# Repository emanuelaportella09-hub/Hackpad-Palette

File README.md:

# Hackpad-Palette
A Hackpad where you can switch colors on Paint for Windows 11.

I tried to make a keyboard for when I use Paint, to change colors like a real palette.

IT ONLY WORKS FOR PAINT ON WINDOWS 11.
IT WON'T WORK FOR OTHER SOFTWARE.

It was fun to make, and it taught me more about the production process of keyboards. It's really interesting, because out there is a whole community that loves this kind of hardware.

# FEATURES
- 128x32 OLED display
- 16 keys
- Can change colors on Paint on Windows 11

# PCB
I used EasyEDA for this project since I know how to use it a little, unlike KiCad.

# SCHEMATICS

# CAD
Plate only

Case and plate

Case, plate, and PCB all together. I couldn't put the 3D file of the PCB in Onshape because it was buggy for some reason, so I decided to put a rectangle inside with the same measurements as the board instead.

# BOM

16x MX Switches

1x XIAO RP2040

16x Differently Colored DSA Keycaps

4x M3x16 Bolt

4x M3 Heatset

1x 0.91" 128x32 OLED Display

16x Through-hole 1N4148 Diodes

1x Case.step in PRODUCTION FOLDER needs to be 3d printed

1x Plate.step in PRODUCTION FOLDER needs to be 3d printed

#**EXTRA NEDDED:**

Soldering Iron

My firmware

Arduino IDE installed on a computer

AutoHotKey installed on a computer

#**TESTING:**

Few Jump Wires

Breadboard

Usb-c to usb cable

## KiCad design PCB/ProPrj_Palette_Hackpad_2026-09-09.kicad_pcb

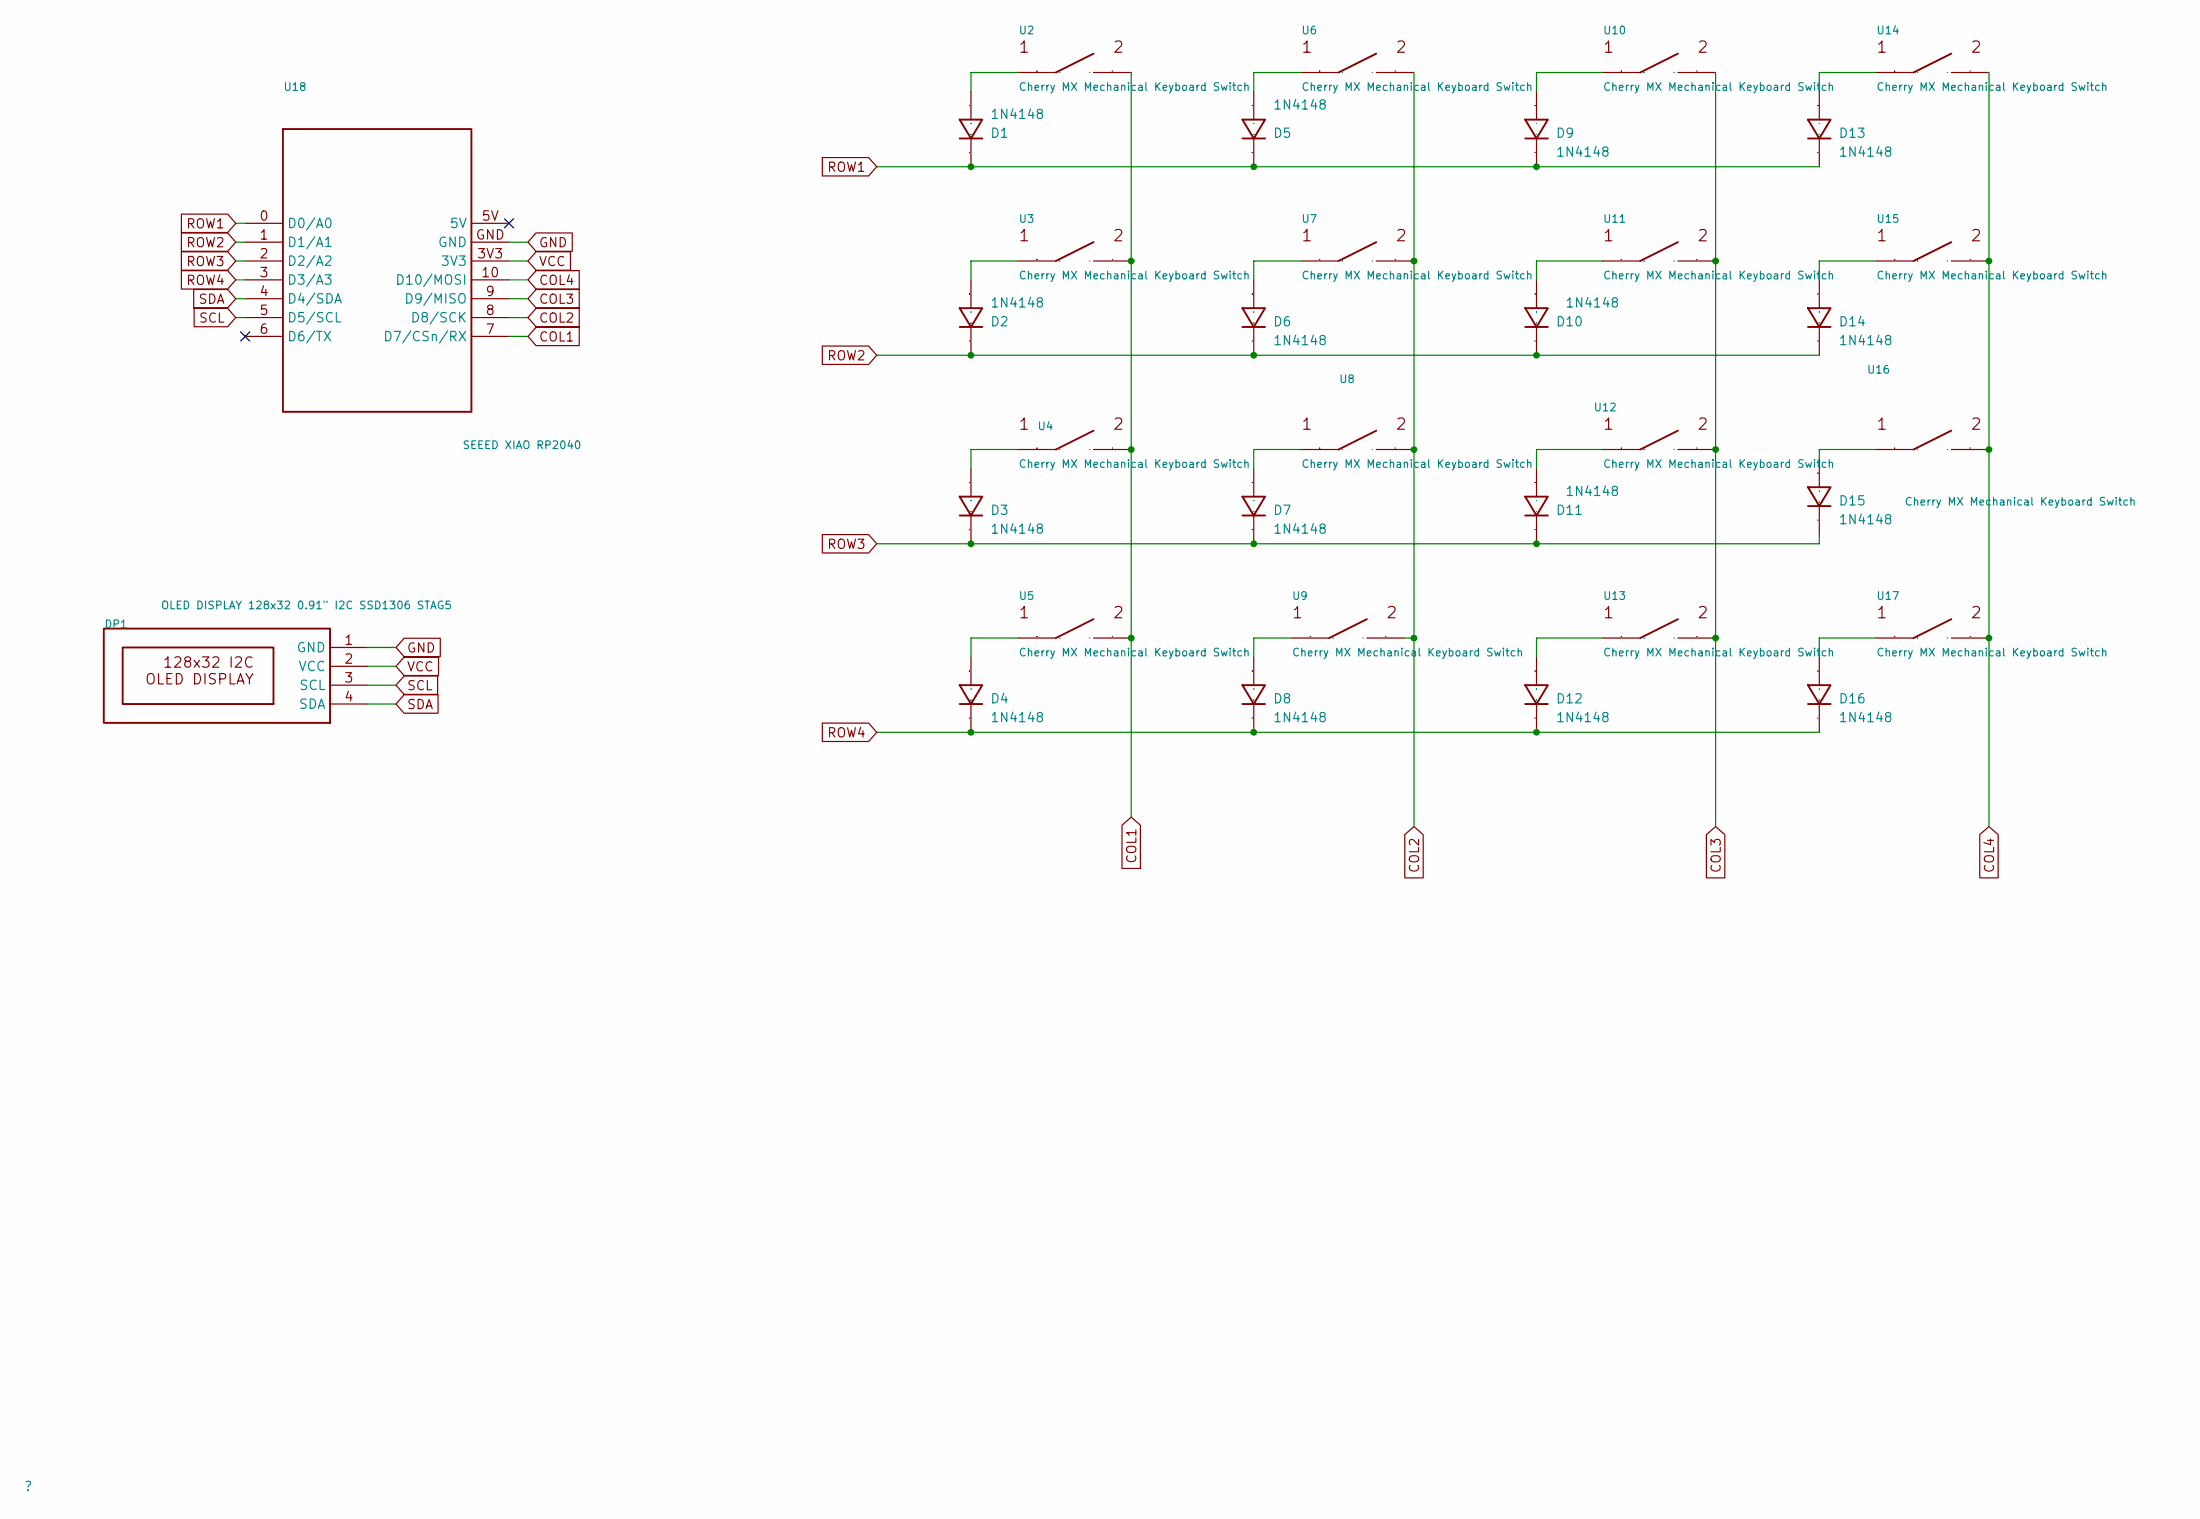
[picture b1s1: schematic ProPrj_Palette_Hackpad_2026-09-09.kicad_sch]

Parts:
D1, D2, D3, D4, D5, D6, D7, D8, D9, D10, D11, D12, D13, D14, D15, D16: 1N4148; DO-35_BD2.0-L4.0-P8.00-D0.5-FD; Manufacturer Part 1N4148; LCSC Part Name 100V 200mA
DP1: OLED DISPLAY 128x32 0.91" I2C SSD1306 STAG5; OLED-TH-C128-R64-D0.91-I2C-SSD1306-STAG5
U2, U3, U4, U5, U6, U7, U8, U9, U10, U11, U12, U13, U14, U15, U16, U17: Cherry MX Mechanical Keyboard Switch; CHERRY MX KEYSWITCH
U18: SEEED XIAO RP2040; XIAO RP2040 V1.22_BOARD

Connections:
$1N3: D1.1 (A), U2.1
$1N4: D2.1 (A), U3.1
$1N5: D3.1 (A), U4.1
$1N7: D4.1 (A), U5.1
$1N8: D5.1 (A), U6.1
$1N9: D6.1 (A), U7.1
$1N10: D7.1 (A), U8.1
$1N11: D8.1 (A), U9.1
$1N12: D9.1 (A), U10.1
$1N13: D10.1 (A), U11.1
$1N14: D11.1 (A), U12.1
$1N15: D12.1 (A), U13.1
$1N17: D13.1 (A), U14.1
$1N18: D14.1 (A), U15.1
$1N21: D15.1 (A), U16.1
$1N22: D16.1 (A), U17.1
COL1: U2.2, U3.2, U4.2, U5.2, U18.7 (D7/CSn/RX)
COL2: U6.2, U7.2, U8.2, U9.2, U18.8 (D8/SCK)
COL3: U10.2, U11.2, U12.2, U13.2, U18.9 (D9/MISO)
COL4: U14.2, U15.2, U16.2, U17.2, U18.10 (D10/MOSI)
GND: DP1.1 (GND), U18.GND
ROW1: D1.2 (K), D5.2 (K), D9.2 (K), D13.2 (K), U18.0 (D0/A0)
ROW2: D2.2 (K), D6.2 (K), D10.2 (K), D14.2 (K), U18.1 (D1/A1)
ROW3: D3.2 (K), D7.2 (K), D11.2 (K), D15.2 (K), U18.2 (D2/A2)
ROW4: D4.2 (K), D8.2 (K), D12.2 (K), D16.2 (K), U18.3 (D3/A3)
SCL: DP1.3 (SCL), U18.5 (D5/SCL)
SDA: DP1.4 (SDA), U18.4 (D4/SDA)
VCC: DP1.2 (VCC), U18.3V3

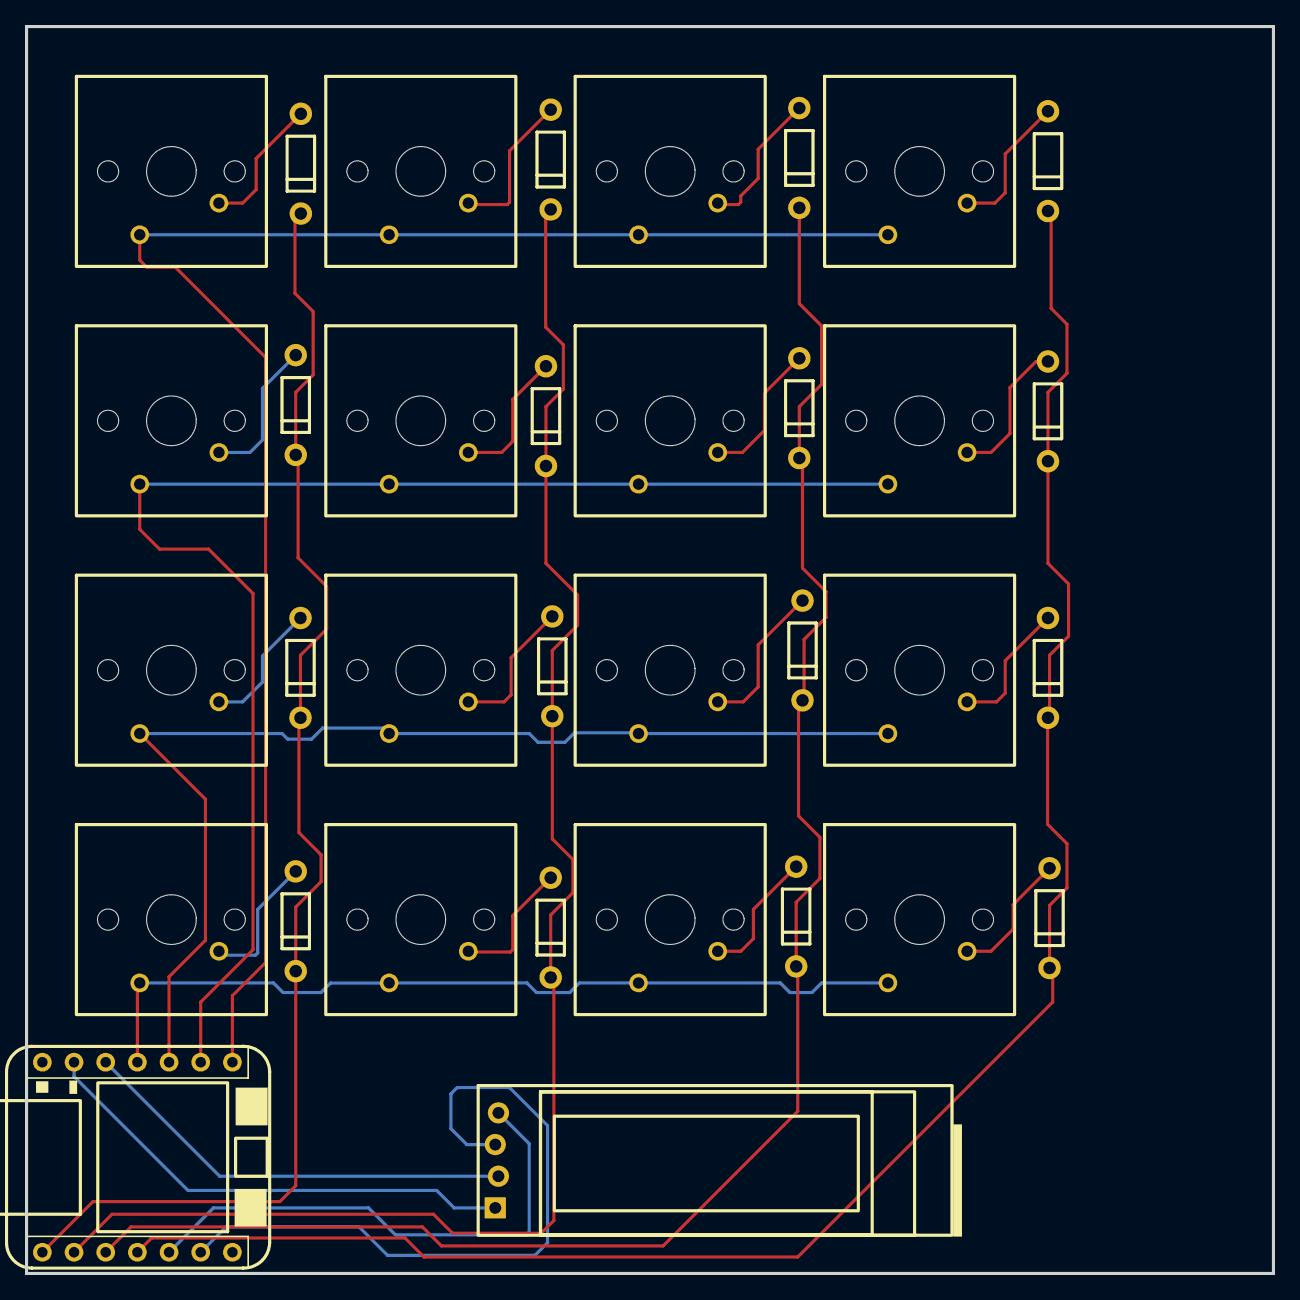
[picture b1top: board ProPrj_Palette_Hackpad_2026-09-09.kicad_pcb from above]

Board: 2 copper layers, 100.0 x 100.0 mm, 34 parts (0 on the bottom side), 28 nets.
